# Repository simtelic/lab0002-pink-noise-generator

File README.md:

# Pink Noise Generator

This kit offers a simple yet effective DIY pink noise generator. It features a compact and user-friendly design that utilizes only three transistors and one operational amplifier, making it a cost-effective and educational option for exploring the unique characteristics of pink noise. All components are through-hole, ensuring that assembly is straightforward and suitable for hobbyists of varying skill levels.

The pink-noise generator operates with a DC power supply ranging from 12V to 18V and includes a single audio output that can be directly connected to a power amplifier or preamplifier for further amplification and playback.

This is an open hardware project, and all design files are available in this repository. You can also [order an unassembled DIY kit from Simtelic](https://simtelic.com/product/pink-noise-generator/), which includes the PCB and all the necessary components for assembly and testing.

[PCBWay](https://www.pcbway.com) sponsors this project, and you can [directly order the PCB](https://www.pcbway.com/project/shareproject/Analog_pink_noise_generator_595b019c.html) from them as well.

The [datasheet](https://simtelic.com/datasheet.php?id=lb0002) and [user manual](https://simtelic.com/datasheet.php?id=lb0002) for this project are available at [simtelic.com](https://simtelic.com).

## Bill of Materials

| Designator               | Value                                                             | Quantity | Notes                                                                               |
|--------------------------|-------------------------------------------------------------------|----------|-------------------------------------------------------------------------------------|
| C101,C103                | [100μF/25V](https://s.click.aliexpress.com/e/_omJ0Eoy)            | 2        |                                                                                     |
| C102,C104                | [1000μF/25V](https://s.click.aliexpress.com/e/_olrI524)           | 2        |                                                                                     |
| C105,C106,C114           | [10μF/25V](https://s.click.aliexpress.com/e/_ompkcr2)             | 3        |                                                                                     |
| C107,C115,C116           | [0.1μF/50V](https://s.click.aliexpress.com/e/_okANxdw)            | 3        |                                                                                     |
| C108                     | [0.033μF/50V](https://s.click.aliexpress.com/e/_onlJl4o)          | 1        |                                                                                     |
| C109                     | [0.01μF/50V](https://s.click.aliexpress.com/e/_okQIYzA)           | 1        |                                                                                     |
| C110                     | [0.0033μF/50V](https://s.click.aliexpress.com/e/_oDFPQX2)         | 1        |                                                                                     |
| C111                     | [0.001μF/50V](https://s.click.aliexpress.com/e/_oDFPQX2)          | 1        |                                                                                     |
| C112                     | [330PF/50V](https://s.click.aliexpress.com/e/_oBugdCo)            | 1        |                                                                                     |
| C113                     | [100PF/50V](https://s.click.aliexpress.com/e/_oBugdCo)            | 1        |                                                                                     |
| R101,R102,R104,R105,R106 | [1KΩ(5% 1W)](https://s.click.aliexpress.com/e/_oFf5dpE)           | 5        |                                                                                     |
| R103,R107                | [2.2Ω(5% 1W)](https://s.click.aliexpress.com/e/_oFf5dpE)          | 2        |                                                                                     |
| R108,R109,R115           | [100KΩ](https://s.click.aliexpress.com/e/_onyWV8u)                | 3        |                                                                                     |
| R110,R111,R117           | [10KΩ](https://s.click.aliexpress.com/e/_onyWV8u)                 | 3        |                                                                                     |
| R112                     | [1.8MΩ](https://s.click.aliexpress.com/e/_onyWV8u)                | 1        |                                                                                     |
| R113                     | [1MΩ](https://s.click.aliexpress.com/e/_onyWV8u)                  | 1        |                                                                                     |
| R114                     | [330KΩ](https://s.click.aliexpress.com/e/_onyWV8u)                | 1        |                                                                                     |
| R116                     | [33KΩ](https://s.click.aliexpress.com/e/_onyWV8u)                 | 1        |                                                                                     |
| R118                     | [3.3KΩ](https://s.click.aliexpress.com/e/_onyWV8u)                | 1        |                                                                                     |
| D101,D102                | [1N4007](https://s.click.aliexpress.com/e/_oC87JiG)               | 2        | https://www.vishay.com/docs/88503/1n4001.pdf                                        |
| Q101                     | [TIP31](https://s.click.aliexpress.com/e/_oDikbdi)                | 1        | https://www.onsemi.com/download/data-sheet/pdf/tip31a-d.pdf                         |
| Q102                     | [TIP32](https://s.click.aliexpress.com/e/_oDikbdi)                | 1        | https://www.onsemi.com/download/data-sheet/pdf/tip32c-d.pdf                         |
| Q103                     | [2SC945](https://s.click.aliexpress.com/e/_oCgKZjW)               | 1        | https://datasheet.octopart.com/2SC945-Inchange-Semiconductor-datasheet-15979352.pdf |
| U101                     | [NJM4558](https://s.click.aliexpress.com/e/_onCjzLQ)              | 1        | https://www.nisshinbo-microdevices.co.jp/en/pdf/datasheet/NJM4558_E.pdf             |
| J101                     | [5.5mm DC Jack Socket](https://s.click.aliexpress.com/e/_o2awuTE) | 1        |                                                                                     |
| J102                     | [RCA Jack Socket](https://s.click.aliexpress.com/e/_oEL5MTS)      | 1        |                                                                                     |
| TP101                    | [Test pin (optional)](https://s.click.aliexpress.com/e/_olBI9cC)  | 1        |                                                                                     |

*All resistors are 5% 1/4W unless otherwise noted*

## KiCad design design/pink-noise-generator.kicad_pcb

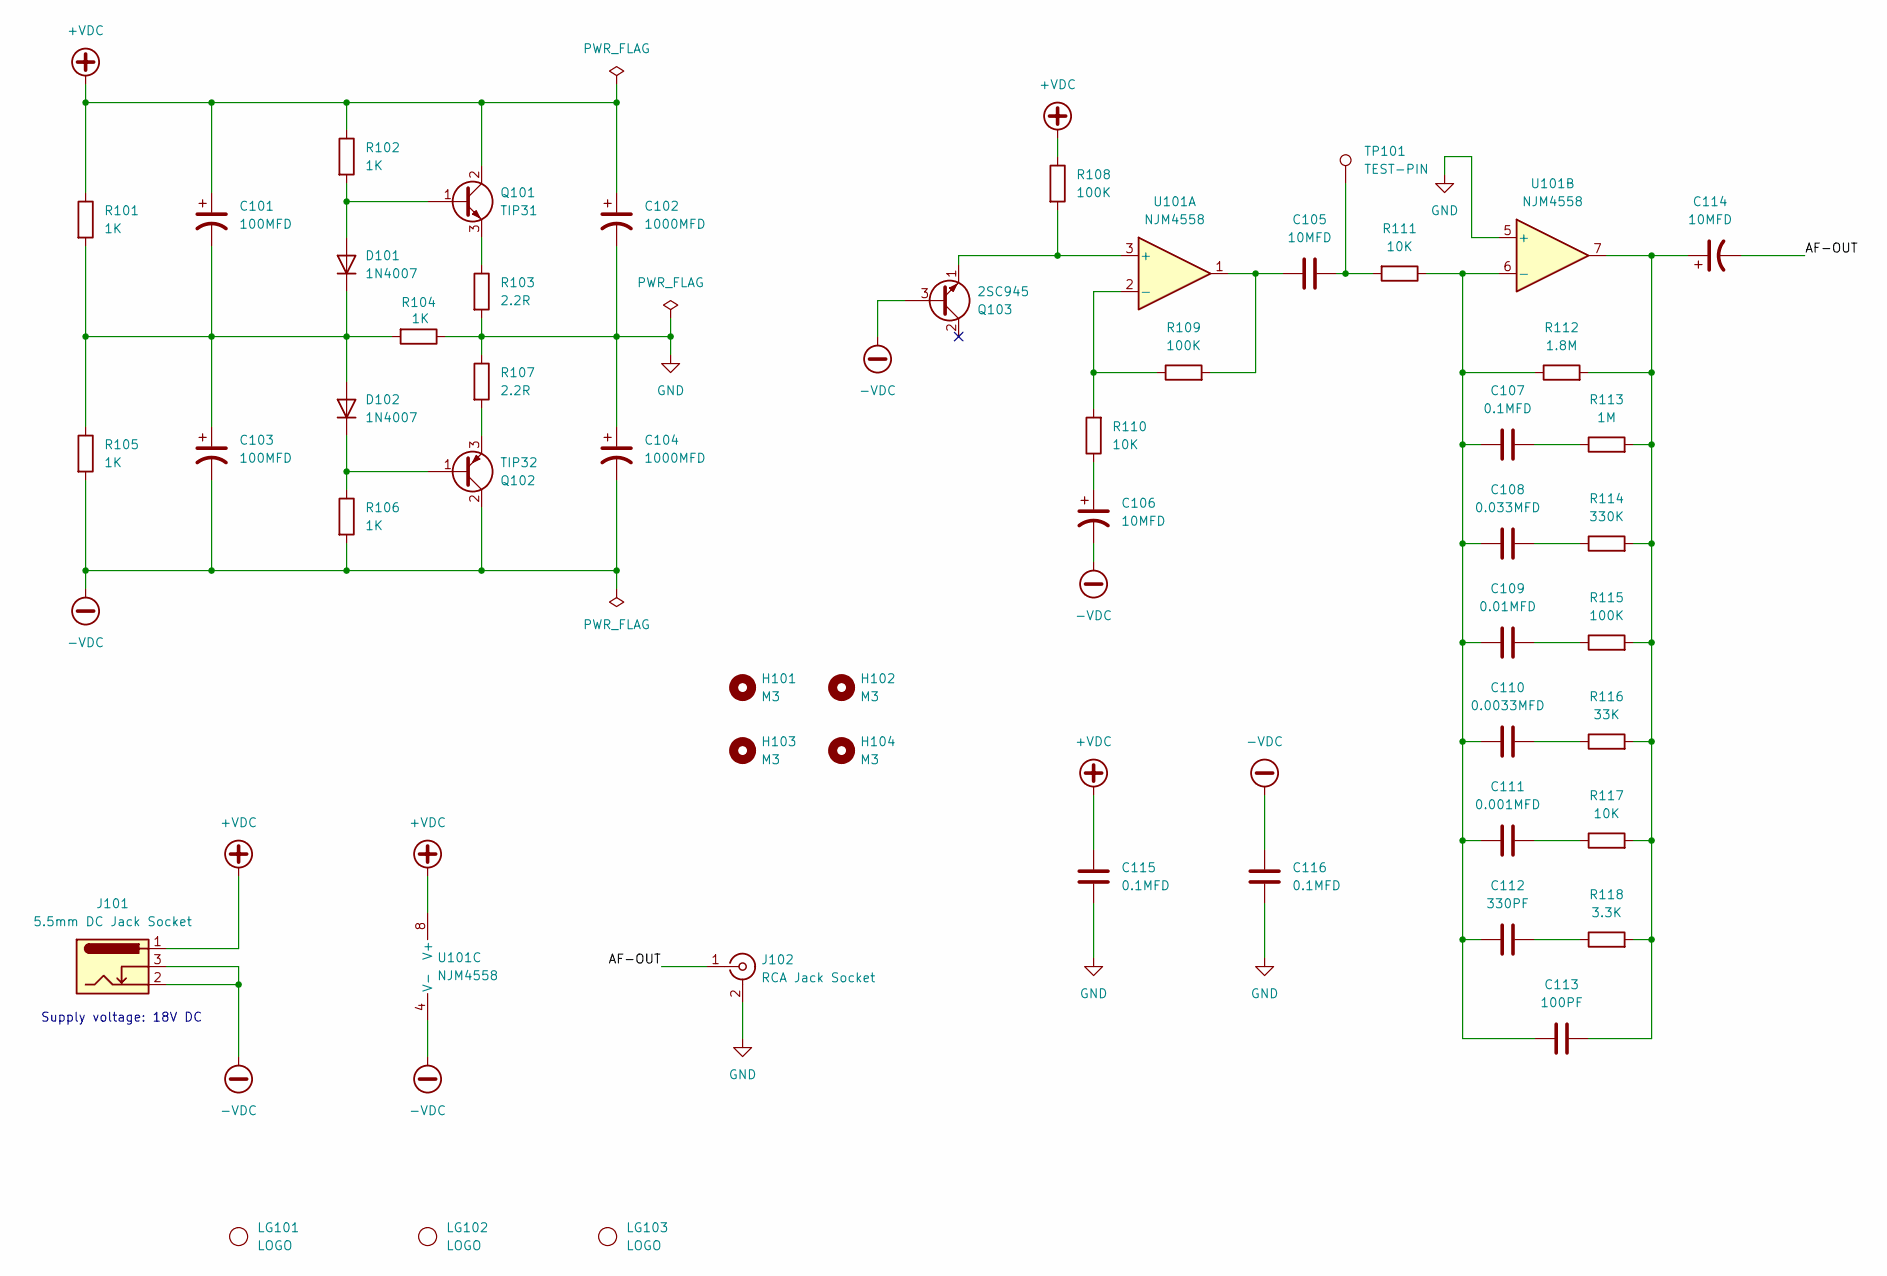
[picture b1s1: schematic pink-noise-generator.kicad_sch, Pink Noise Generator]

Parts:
C101, C103: 100MFD; CP_Radial_D6.3mm_P2.50mm
C102, C104: 1000MFD; CP_Radial_D12.5mm_P5.00mm
C105, C106, C114: 10MFD; CP_Radial_D5.0mm_P2.50mm
C107, C115, C116: 0.1MFD; C_Disc_D10.5mm_W5.0mm_P7.50mm
C108: 0.033MFD; C_Disc_D7.5mm_W5.0mm_P5.00mm
C109: 0.01MFD; C_Disc_D5.0mm_W2.5mm_P5.00mm
C110: 0.0033MFD; C_Disc_D5.0mm_W2.5mm_P5.00mm
C111: 0.001MFD; C_Disc_D5.0mm_W2.5mm_P5.00mm
C112: 330PF; C_Disc_D4.7mm_W2.5mm_P5.00mm
C113: 100PF; C_Disc_D4.7mm_W2.5mm_P5.00mm
D101, D102: 1N4007; D_DO-41_SOD81_P10.16mm_Horizontal
H101, H102, H103, H104: M3; MountingHole_3.2mm_M3_Pad
J101: 5.5mm DC Jack Socket; BarrelJack_Horizontal
J102: RCA Jack Socket; RCA Socket
LG101: LOGO; simtelic-5
LG102, LG103: LOGO; simtelic-name-5
Q101: TIP31; TO-220-3_Vertical
Q102: TIP32; TO-220-3_Vertical
Q103: 2SC945; TO-92L_HandSolder
R101, R102, R104, R105, R106: 1K; R_Axial_DIN0414_L11.9mm_D4.5mm_P15.24mm_Horizontal
R103, R107: 2.2R; R_Axial_DIN0414_L11.9mm_D4.5mm_P15.24mm_Horizontal
R108, R109, R115: 100K; R_Axial_DIN0207_L6.3mm_D2.5mm_P10.16mm_Horizontal
R110, R111, R117: 10K; R_Axial_DIN0207_L6.3mm_D2.5mm_P10.16mm_Horizontal
R112: 1.8M; R_Axial_DIN0207_L6.3mm_D2.5mm_P10.16mm_Horizontal
R113: 1M; R_Axial_DIN0207_L6.3mm_D2.5mm_P10.16mm_Horizontal
R114: 330K; R_Axial_DIN0207_L6.3mm_D2.5mm_P10.16mm_Horizontal
R116: 33K; R_Axial_DIN0207_L6.3mm_D2.5mm_P10.16mm_Horizontal
R118: 3.3K; R_Axial_DIN0207_L6.3mm_D2.5mm_P10.16mm_Horizontal
TP101: TEST-PIN; TestPoint_THTPad_2.5x2.5mm_Drill1.2mm
U101: NJM4558; DIP-8_W7.62mm_LongPads

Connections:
+VDC: C101.1, C102.1, C115.1, J101.1, Q101.2 (C), R101.1, R102.1, R108.1, U101.8 (V+)
-VDC: C103.2, C104.2, C106.2, C116.1, J101.2, J101.3, Q102.2 (C), Q103.3 (B), R105.2, R106.2, U101.4 (V-)
/AF-OUT: C114.2, J102.1 (In)
GND: C102.2, C104.1, C115.2, C116.2, J102.2 (Ext), R103.2, R104.1, R107.1, U101.5 (+)
unnamed: C105.1, R109.2, U101.1
unnamed: C105.2, R111.2, TP101.1
unnamed: C106.1, R110.1
unnamed: C107.2, R113.1
unnamed: C108.2, R114.1
unnamed: C109.2, R115.1
unnamed: C110.2, R116.1
unnamed: C111.2, R117.1
unnamed: C112.2, R118.1
unnamed: C113.2, C114.1, R112.2, R113.2, R114.2, R115.2, R116.2, R117.2, R118.2, U101.7
unnamed: D101.2 (A), Q101.1 (B), R102.2
unnamed: C101.2, C103.1, D101.1 (K), D102.2 (A), R101.2, R104.2, R105.1
unnamed: D102.1 (K), Q102.1 (B), R106.1
unnamed: Q101.3 (E), R103.1
unnamed: Q102.3 (E), R107.2
unnamed: Q103.1 (E), R108.2, U101.3 (+)
unnamed: R109.1, R110.2, U101.2 (-)
unnamed: C107.1, C108.1, C109.1, C110.1, C111.1, C112.1, C113.1, R111.1, R112.1, U101.6 (-)

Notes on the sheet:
Supply voltage: 18V DC

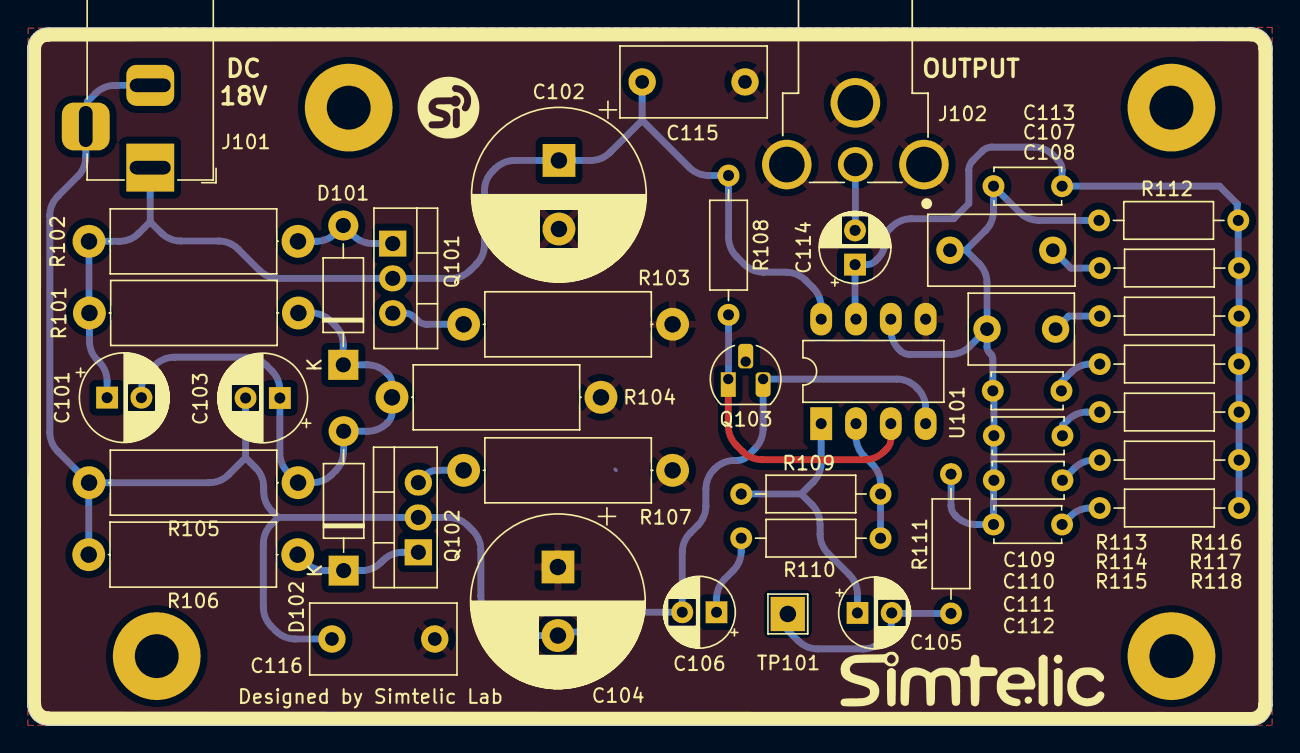
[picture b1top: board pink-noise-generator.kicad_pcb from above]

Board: 2 copper layers, 90.8 x 50.9 mm, 50 parts (1 on the bottom side), 22 nets.

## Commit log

2025-03-05 Initial version of design files.
2025-03-05 Add image of the prototype build.
2025-03-05 Add license file and update links in readme file.
